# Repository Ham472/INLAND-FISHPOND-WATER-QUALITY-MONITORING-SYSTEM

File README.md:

# INLAND-FISHPOND-WATER-QUALITY-MONITORING-SYSTEM

# Collaborators
1. Masika Stephanie - Supervisor
# Inland Fishpond Water Quality Monitoring System

## Overview
This project is an embedded system designed to monitor water quality in an inland fishpond.  
It detects possible water impurities by measuring key environmental parameters using multiple sensors and displays the results in real time.

The system is built around an Arduino Uno and is intended for monitoring, demonstration, and educational purposes.

---

## Parameters Monitored
The system measures the following water and environmental parameters:

- **pH level** – to determine acidity or alkalinity of the water  
- **Water presence / conductivity** – to detect impurities or water conditions  
- **Temperature and humidity** – for environmental monitoring around the fishpond  

---

## Hardware Components
- Arduino Uno R3  
- pH Sensor Module  
- Water Sensor  
- DHT11 Temperature and Humidity Sensor  
- 16×2 LCD Display  
- PCF8574 I²C I/O Expander  
- Potentiometers (for calibration and contrast control)  
- Passive components (resistors, capacitors, inductor)  

---

## System Description
- Sensor data is read by the Arduino through analog and digital inputs.  
- The pH sensor provides analog voltage corresponding to the water’s pH level.  
- The water sensor detects changes in water conductivity, indicating possible impurities.  
- The DHT11 sensor measures ambient temperature and humidity.  
- Collected data is displayed on a 16×2 LCD using an I²C interface to reduce pin usage.  

---

## Software & Tools
- Arduino IDE  
- Proteus (for circuit simulation)  
- Embedded C / Arduino programming language  

---

## Usage
1. Power the system with a 5V supply.
2. Place the pH probe and water sensor in the fishpond water.
3. The Arduino reads sensor data continuously.
4. Measured values are displayed on the LCD in real time.

---

## Project Status
Ongoing / Prototype Stage 
Further improvements may include data logging, wireless transmission, and alert systems.

---

## Applications
- Inland fishpond monitoring  
- Water quality analysis  
- Embedded systems learning and simulation  
- Environmental monitoring projects  

---

## Author
Ham Karisa
Julius Mwangi

---

## License
This project is intended for educational and academic use.

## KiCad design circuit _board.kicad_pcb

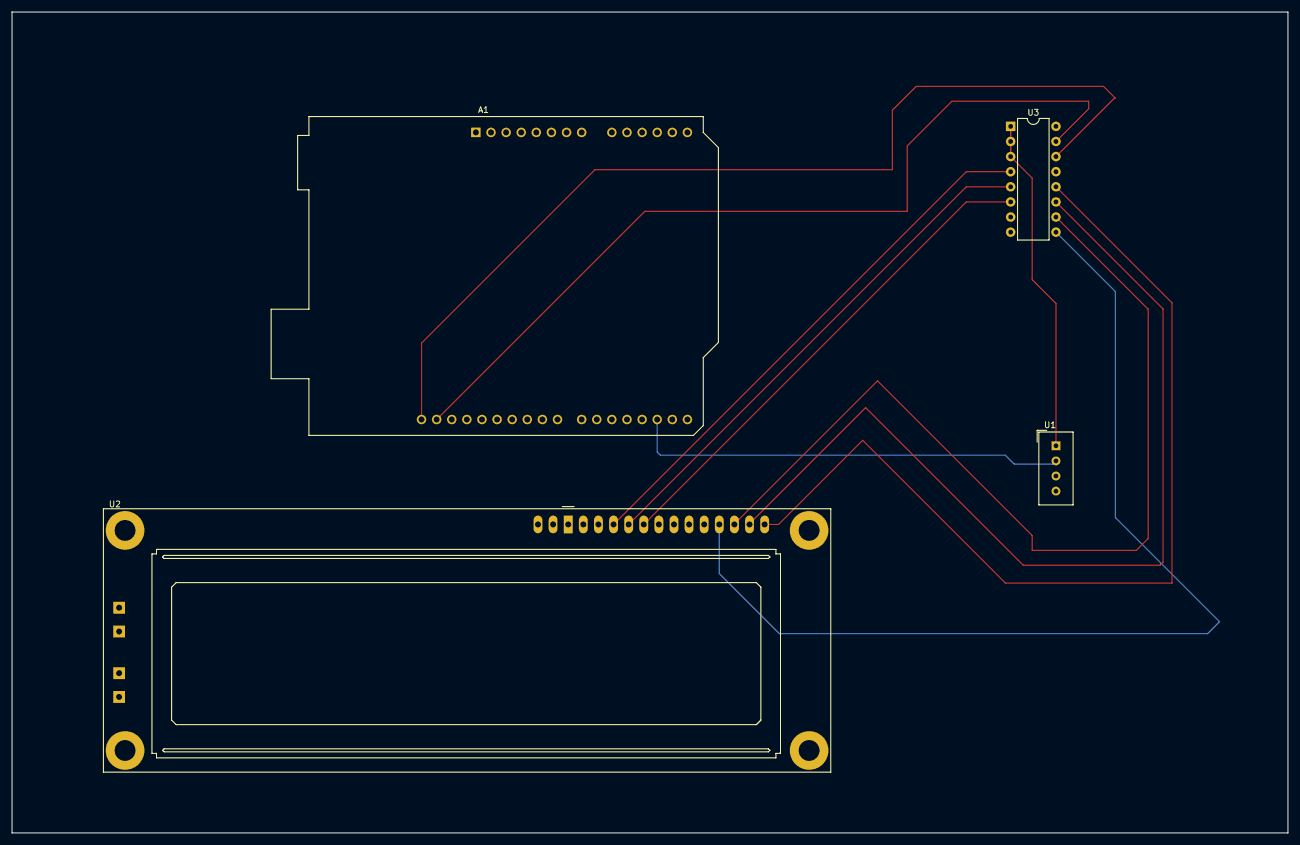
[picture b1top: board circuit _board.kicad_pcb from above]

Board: 2 copper layers, 214.5 x 138.0 mm, 4 parts (0 on the bottom side), 11 nets.

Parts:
A1: Arduino_UNO_R3
U1: DHT11; Aosong_DHT11_5.5x12.0_P2.54mm
U2: LCD-016N002L
U3: PCF8574P; DIP-16_W7.62mm

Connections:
+5V: U1.1 (VDD), U3.1 (A0), U3.2 (A1), U3.3 (A2)
unnamed: A1.17 (D2), U1.2 (DATA)
unnamed: U2.11 (DB4), U3.9 (P4)
unnamed: U2.12 (DB5), U3.10 (P5)
unnamed: U2.13 (DB6), U3.11 (P6)
unnamed: U2.14 (DB7), U3.12 (P7)
unnamed: U2.6 (E), U3.6 (P2)
unnamed: U2.4 (RS), U3.4 (P0)
unnamed: U2.5 (R/~W), U3.5 (P1)
unnamed: A1.32 (SCL/A5), U3.14 (SCL)
unnamed: A1.31 (SDA/A4), U3.15 (SDA)

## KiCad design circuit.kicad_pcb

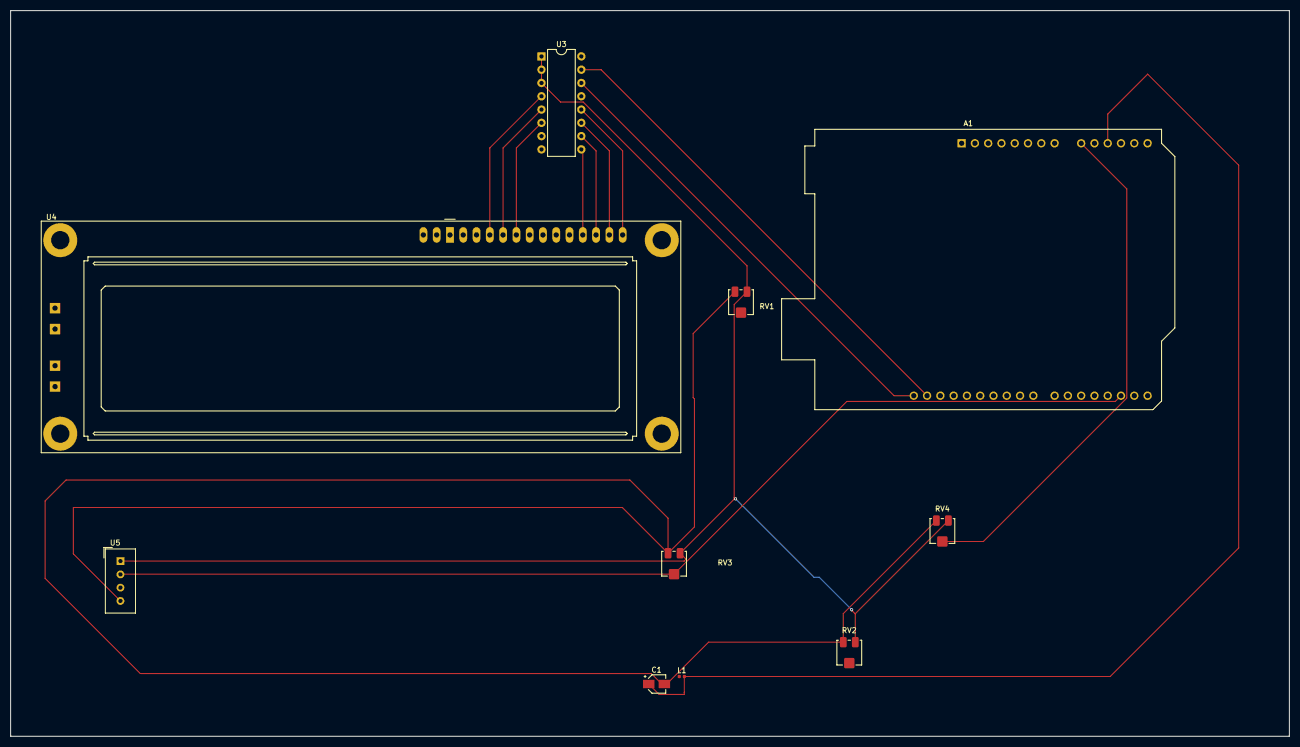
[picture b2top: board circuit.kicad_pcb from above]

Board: 2 copper layers, 244.5 x 138.8 mm, 10 parts (0 on the bottom side), 14 nets.

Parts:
A1: Arduino_UNO_R3
C1: C_Polarized_Small_US; CP_Elec_3x5.3
L1: L_Small; L_0402_1005Metric
RV1, RV2, RV3, RV4: R_Potentiometer; Potentiometer_Bourns_3314J_Vertical
U3: PCF8574P; DIP-16_W7.62mm
U4: LCD-016N002L
U5: DHT11; Aosong_DHT11_5.5x12.0_P2.54mm

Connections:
+5V: RV1.3, RV2.3, RV3.3, RV4.3, U3.1 (A0), U3.2 (A1), U3.3 (A2), U5.1 (VDD)
Earth: C1.2, RV1.1, RV2.1, RV3.1, RV4.1, U5.4 (GND)
unnamed: A1.9 (A0), RV4.2
unnamed: A1.11 (A2), C1.1, L1.2
unnamed: A1.17 (D2), RV3.2, U5.2 (DATA)
unnamed: U3.4 (P0), U4.4 (RS)
unnamed: U3.5 (P1), U4.5 (R/~W)
unnamed: U3.6 (P2), U4.6 (E)
unnamed: U3.9 (P4), U4.11 (DB4)
unnamed: U3.10 (P5), U4.12 (DB5)
unnamed: U3.11 (P6), U4.13 (DB6)
unnamed: U3.12 (P7), U4.14 (DB7)
unnamed: A1.32 (SCL/A5), U3.14 (SCL)
unnamed: A1.31 (SDA/A4), U3.15 (SDA)
